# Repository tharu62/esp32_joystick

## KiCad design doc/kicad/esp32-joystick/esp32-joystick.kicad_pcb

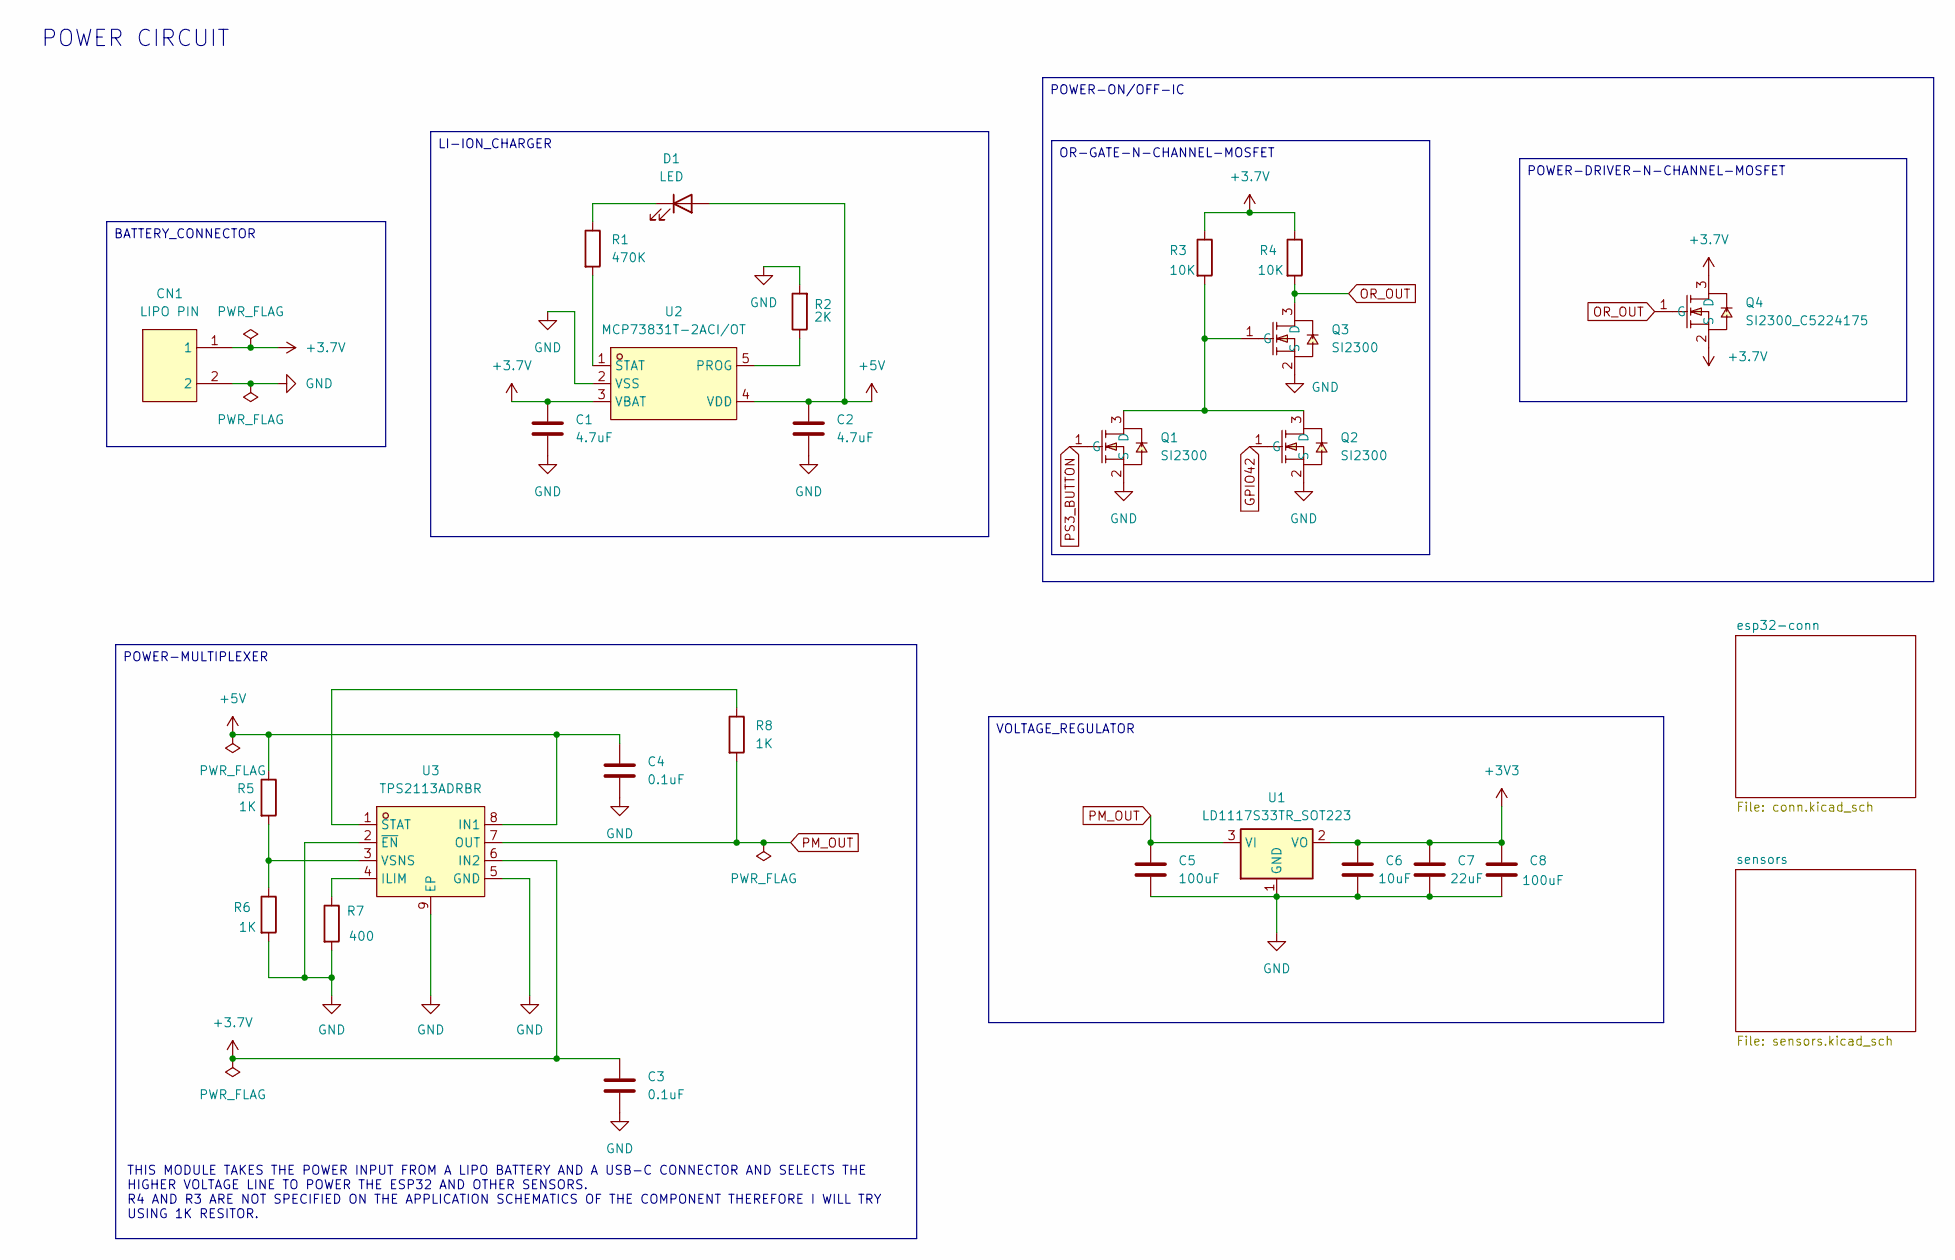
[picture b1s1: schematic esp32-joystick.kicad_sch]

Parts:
C1, C2: 4.7uF; C1206
C3, C4: 0.1uF; C1206
C5, C8: 100uF; C1206
C6: 10uF; C1206
C7: 22uF; C1206
CN1: LIPO PIN; CONN-TH_B2B-PH-K-S; LCSC Part C131337
D1: LED; LED1206-FD
Q1, Q2, Q3: SI2300; SOT-23-3_L2.9-W1.3-P1.90-LS2.4-BR; LCSC Part C5224175
Q4: SI2300_C5224175; SOT-23-3_L2.9-W1.3-P1.90-LS2.4-BR; LCSC Part C5224175
R1: 470K; R0603
R2: 2K; R0603
R3, R4: 10K; R0603
R5, R6, R8: 1K; R0603
R7: 400; R0805
U1: LD1117S33TR_SOT223; SOT-223-3_TabPin2
U2: MCP73831T-2ACI/OT; SOT-23-5_L3.0-W1.7-P0.95-LS2.8-BL; LCSC Part C424093
U3: TPS2113ADRBR; SON-8_L3.0-W3.0-P0.65-LS3.0-BL-EP; LCSC Part C354512

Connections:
+3.7V: C1.1, C3.1, CN1.1, Q4.2 (S), Q4.3 (D), R3.1, R4.1, U2.3 (VBAT), U3.6 (IN2)
+3V3: C6.1, C7.1, C8.1, U1.2 (VO); also elsewhere on the board
+5V: C2.1, C4.1, D1.2 (A), R5.1, U2.4 (VDD), U3.8 (IN1); also elsewhere on the board
GND: C1.2, C2.2, C3.2, C4.2, C5.2, C6.2, C7.2, C8.2, CN1.2, Q1.2 (S), Q2.2 (S), Q3.2 (S), R2.2, R6.2, R7.2, U1.1 (GND), U2.2 (VSS), U3.2 (~EN), U3.5 (GND), U3.9 (EP); also elsewhere on the board
GPIO42: Q2.1 (G); also elsewhere on the board
unnamed: D1.1 (K), R1.1
unnamed: Q1.3 (D), Q2.3 (D), Q3.1 (G), R3.2
unnamed: R2.1, U2.5 (PROG)
unnamed: R1.2, U2.1 (STAT)
unnamed: R7.1, U3.4 (ILIM)
unnamed: R8.1, U3.1 (STAT)
unnamed: R5.2, R6.1, U3.3 (VSNS)
OR_OUT: Q3.3 (D), Q4.1 (G), R4.2
PM_OUT: C5.1, R8.2, U1.3 (VI), U3.7 (OUT)
PS3_BUTTON: Q1.1 (G); also elsewhere on the board

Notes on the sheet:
THIS MODULE TAKES THE POWER INPUT FROM A LIPO BATTERY AND A USB-C CONNECTOR AND SELECTS THE HIGHER VOLTAGE LINE TO POWER THE ESP32 AND OTHER SENSORS. R4 AND R3 ARE NOT SPECIFIED ON THE APPLICATION SCHEMATICS OF THE COMPONENT THEREFORE I WILL TRY USING 1K RESITOR.
POWER CIRCUIT
POWER-MULTIPLEXER
OR-GATE-N-CHANNEL-MOSFET
VOLTAGE_REGULATOR
BATTERY_CONNECTOR
POWER-DRIVER-N-CHANNEL-MOSFET
POWER-ON/OFF-IC
LI-ION_CHARGER

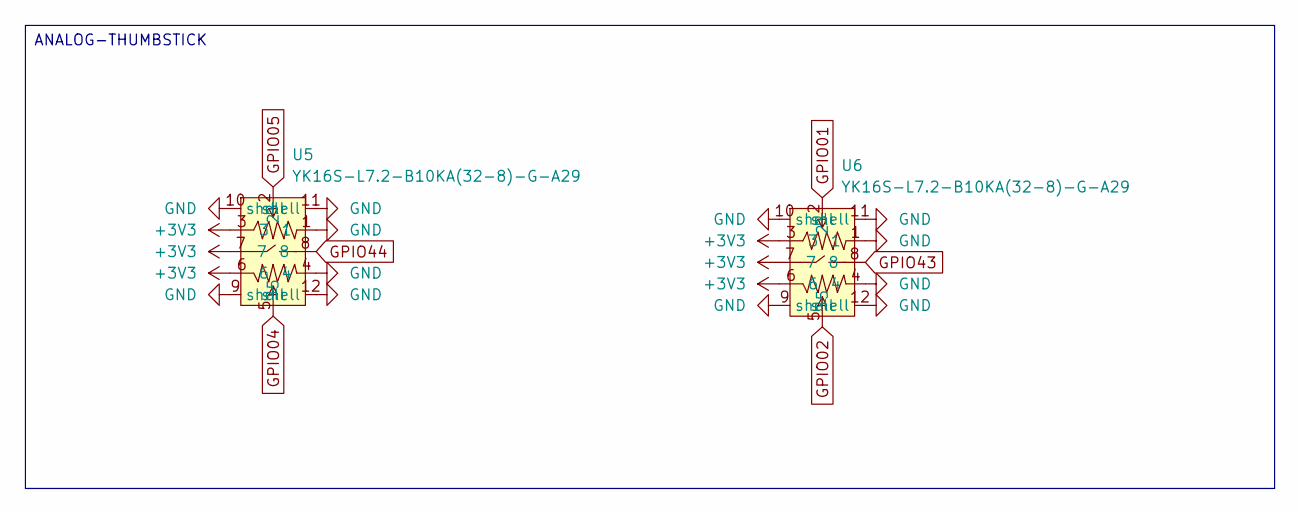
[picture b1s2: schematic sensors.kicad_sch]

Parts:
U5, U6: YK16S-L7.2-B10KA(32-8)-G-A29; JOYTICK-TH_YF16S-FL7.2-B5KB-45-10-Y_1; LCSC Part C37323746

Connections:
+3V3: U5.3, U5.6, U5.7, U6.3, U6.6, U6.7; also elsewhere on the board
GND: U5.1, U5.4, U5.9 (shell), U5.10 (shell), U5.11 (shell), U5.12 (shell), U6.1, U6.4, U6.9 (shell), U6.10 (shell), U6.11 (shell), U6.12 (shell); also elsewhere on the board
GPIO01: U6.2; also elsewhere on the board
GPIO02: U6.5; also elsewhere on the board
GPIO04: U5.5; also elsewhere on the board
GPIO05: U5.2; also elsewhere on the board
GPIO43: U6.8; also elsewhere on the board
GPIO44: U5.8; also elsewhere on the board

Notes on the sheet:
ANALOG-THUMBSTICK

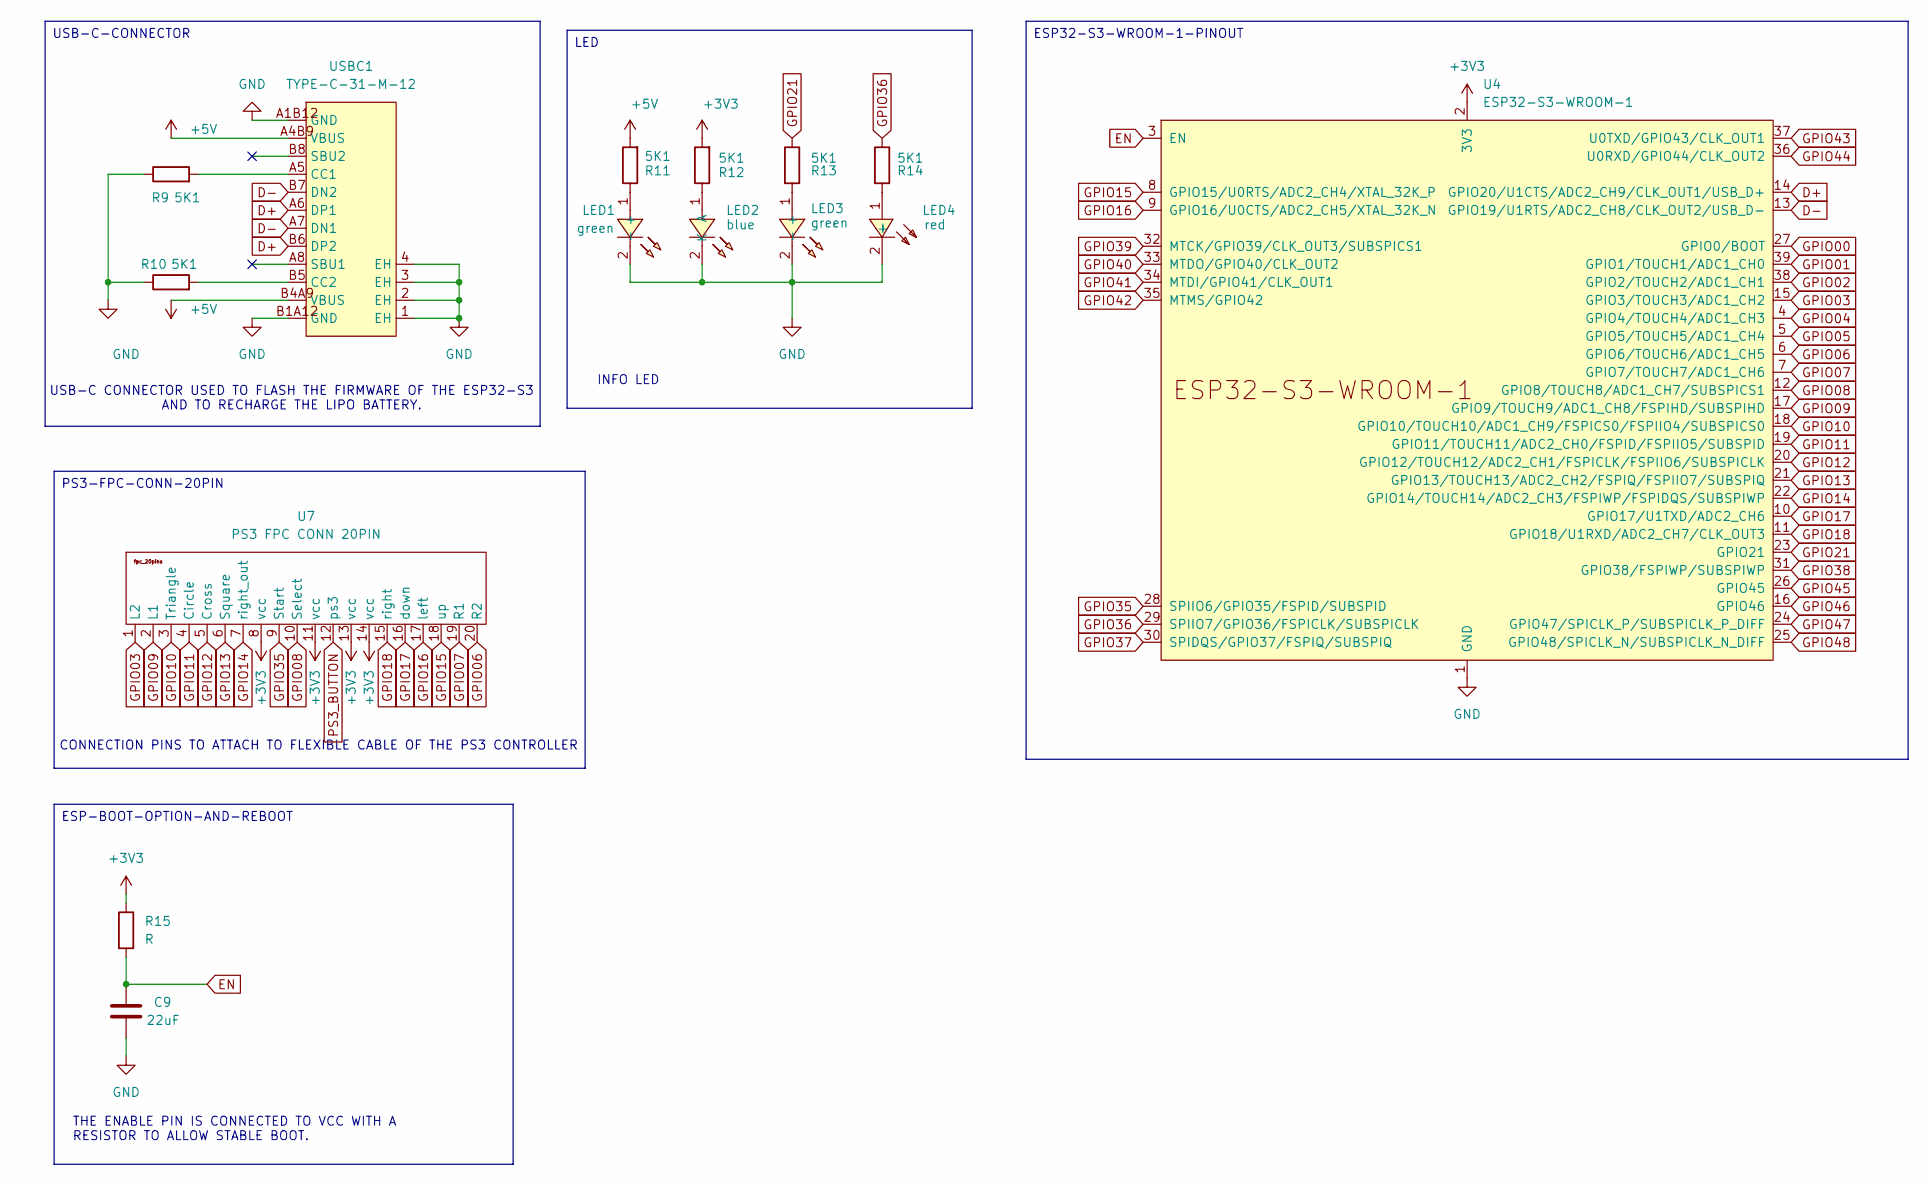
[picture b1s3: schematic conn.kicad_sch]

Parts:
C9: 22uF; C1206
LED1, LED3: green; LED0603-FD; LCSC Part C19273151
LED2: blue; LED0603-FD; LCSC Part C19171394
LED4: red; LED0603-FD; LCSC Part C19171390
R9, R10, R11, R12, R13, R14: 5K1; R0603
R15: R; R0603
U4: ESP32-S3-WROOM-1
U7: PS3 FPC CONN 20PIN; ps3_fpc_conn_20pin
USBC1: TYPE-C-31-M-12; USB-C_SMD-TYPE-C-31-M-12_1; LCSC Part C165948

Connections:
+3V3: R12.2, R15.1, U4.2 (3V3), U7.8 (vcc), U7.11 (vcc), U7.13 (vcc), U7.14 (vcc); also elsewhere on the board
+5V: R11.2, USBC1.A4B9 (VBUS), USBC1.B4A9 (VBUS); also elsewhere on the board
D+: U4.14 (GPIO20/U1CTS/ADC2_CH9/CLK_OUT1/USB_D+), USBC1.A6 (DP1), USBC1.B6 (DP2)
D-: U4.13 (GPIO19/U1RTS/ADC2_CH8/CLK_OUT2/USB_D-), USBC1.A7 (DN1), USBC1.B7 (DN2)
EN: C9.1, R15.2, U4.3 (EN)
GND: C9.2, LED1.2 (-), LED2.2 (K), LED3.2 (-), LED4.2 (-), R9.1, R10.1, U4.1 (GND), U4.40 (GND), U4.41 (GND), USBC1.1 (EH), USBC1.2 (EH), USBC1.3 (EH), USBC1.4 (EH), USBC1.A1B12 (GND), USBC1.B1A12 (GND); also elsewhere on the board
GPIO00: U4.27 (GPIO0/BOOT)
GPIO01: U4.39 (GPIO1/TOUCH1/ADC1_CH0); also elsewhere on the board
GPIO02: U4.38 (GPIO2/TOUCH2/ADC1_CH1); also elsewhere on the board
GPIO03: U4.15 (GPIO3/TOUCH3/ADC1_CH2), U7.1 (L2)
GPIO04: U4.4 (GPIO4/TOUCH4/ADC1_CH3); also elsewhere on the board
GPIO05: U4.5 (GPIO5/TOUCH5/ADC1_CH4); also elsewhere on the board
GPIO06: U4.6 (GPIO6/TOUCH6/ADC1_CH5), U7.20 (R2)
GPIO07: U4.7 (GPIO7/TOUCH7/ADC1_CH6), U7.19 (R1)
GPIO08: U4.12 (GPIO8/TOUCH8/ADC1_CH7/SUBSPICS1), U7.10 (Select)
GPIO09: U4.17 (GPIO9/TOUCH9/ADC1_CH8/FSPIHD/SUBSPIHD), U7.2 (L1)
GPIO10: U4.18 (GPIO10/TOUCH10/ADC1_CH9/FSPICS0/FSPIIO4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), U7.3 (Triangle)
GPIO11: U4.19 (GPIO11/TOUCH11/ADC2_CH0/FSPID/FSPIIO5/S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), U7.4 (Circle)
GPIO12: U4.20 (GPIO12/TOUCH12/ADC2_CH1/FSPICLK/FSPIIO6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), U7.5 (Cross)
GPIO13: U4.21 (GPIO13/TOUCH13/ADC2_CH2/FSPIQ/FSPIIO7/S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), U7.6 (Square)
GPIO14: U4.22 (GPIO14/TOUCH14/ADC2_CH3/FSPIWP/FSPIDQS/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), U7.7 (right_out)
GPIO15: U4.8 (GPIO15/U0RTS/ADC2_CH4/XTAL_32K_P), U7.18 (up)
GPIO16: U4.9 (GPIO16/U0CTS/ADC2_CH5/XTAL_32K_N), U7.17 (left)
GPIO17: U4.10 (GPIO17/U1TXD/ADC2_CH6), U7.16 (down)
GPIO18: U4.11 (GPIO18/U1RXD/ADC2_CH7/CLK_OUT3), U7.15 (right)
GPIO21: R13.1, U4.23 (GPIO21)
GPIO35: U4.28 (SPIIO6/GPIO35/FSPID/SUBSPID), U7.9 (Start)
GPIO36: R14.1, U4.29 (SPIIO7/GPIO36/FSPICLK/SUBSPICLK)
GPIO37: U4.30 (SPIDQS/GPIO37/FSPIQ/SUBSPIQ)
GPIO38: U4.31 (GPIO38/FSPIWP/SUBSPIWP)
GPIO39: U4.32 (MTCK/GPIO39/CLK_OUT3/SUBSPICS1)
GPIO40: U4.33 (MTDO/GPIO40/CLK_OUT2)
GPIO41: U4.34 (MTDI/GPIO41/CLK_OUT1)
GPIO42: U4.35 (MTMS/GPIO42); also elsewhere on the board
GPIO43: U4.37 (U0TXD/GPIO43/CLK_OUT1); also elsewhere on the board
GPIO44: U4.36 (U0RXD/GPIO44/CLK_OUT2); also elsewhere on the board
GPIO45: U4.26 (GPIO45)
GPIO46: U4.16 (GPIO46)
GPIO47: U4.24 (GPIO47/SPICLK_P/SUBSPICLK_P_DIFF)
GPIO48: U4.25 (GPIO48/SPICLK_N/SUBSPICLK_N_DIFF)
unnamed 42: LED1.1 (+), R11.1; also elsewhere on the board
unnamed 43: LED2.1 (A), R12.1; also elsewhere on the board
unnamed: LED3.1 (+), R13.2
unnamed: LED4.1 (+), R14.2
unnamed: R9.2, USBC1.A5 (CC1)
unnamed: R10.2, USBC1.B5 (CC2)
PS3_BUTTON: U7.12 (ps3); also elsewhere on the board

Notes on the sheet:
THE ENABLE PIN IS CONNECTED TO VCC WITH A RESISTOR TO ALLOW STABLE BOOT.
USB-C CONNECTOR USED TO FLASH THE FIRMWARE OF THE ESP32-S3 AND TO RECHARGE THE LIPO BATTERY.
CONNECTION PINS TO ATTACH TO FLEXIBLE CABLE OF THE PS3 CONTROLLER
INFO LED
PS3-FPC-CONN-20PIN
USB-C-CONNECTOR
LED
ESP32-S3-WROOM-1-PINOUT
ESP-BOOT-OPTION-AND-REBOOT

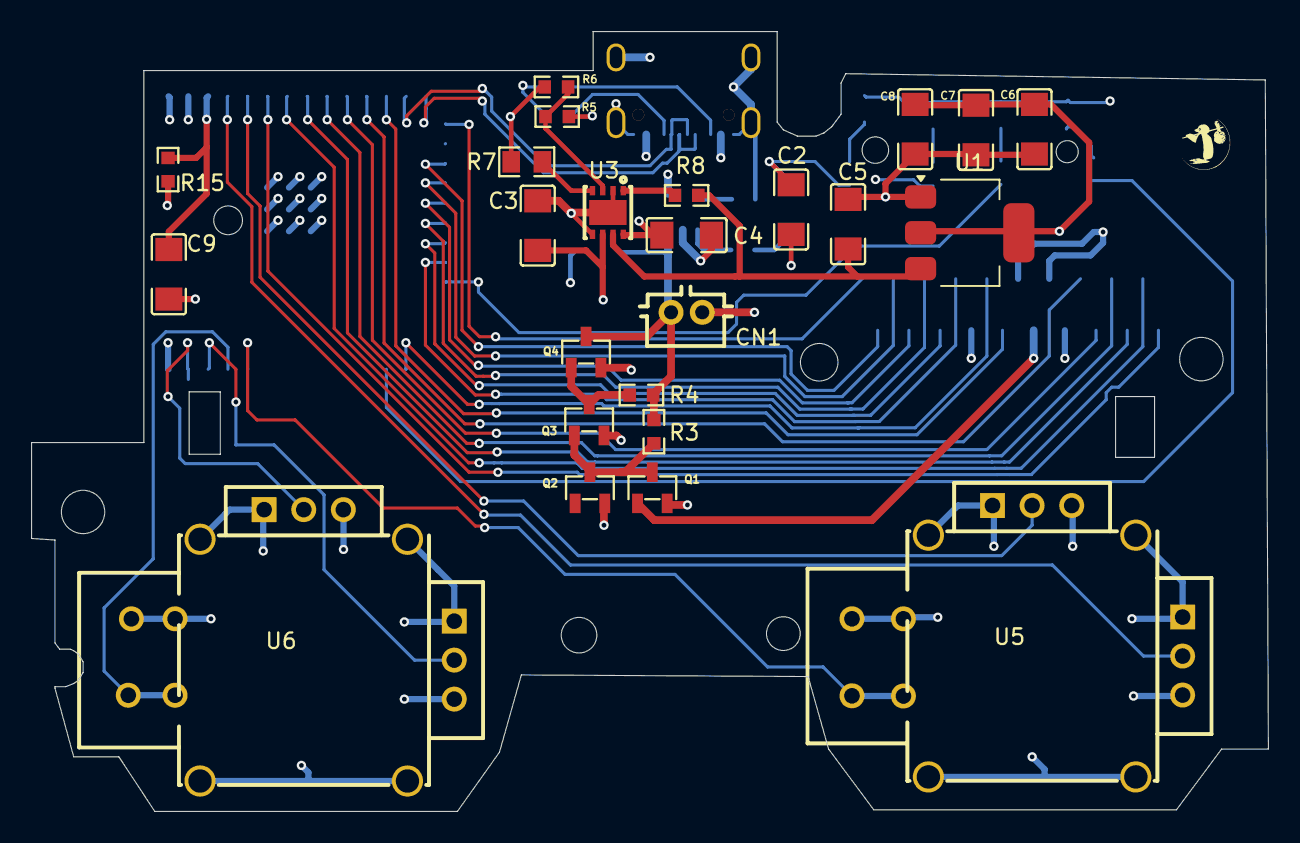
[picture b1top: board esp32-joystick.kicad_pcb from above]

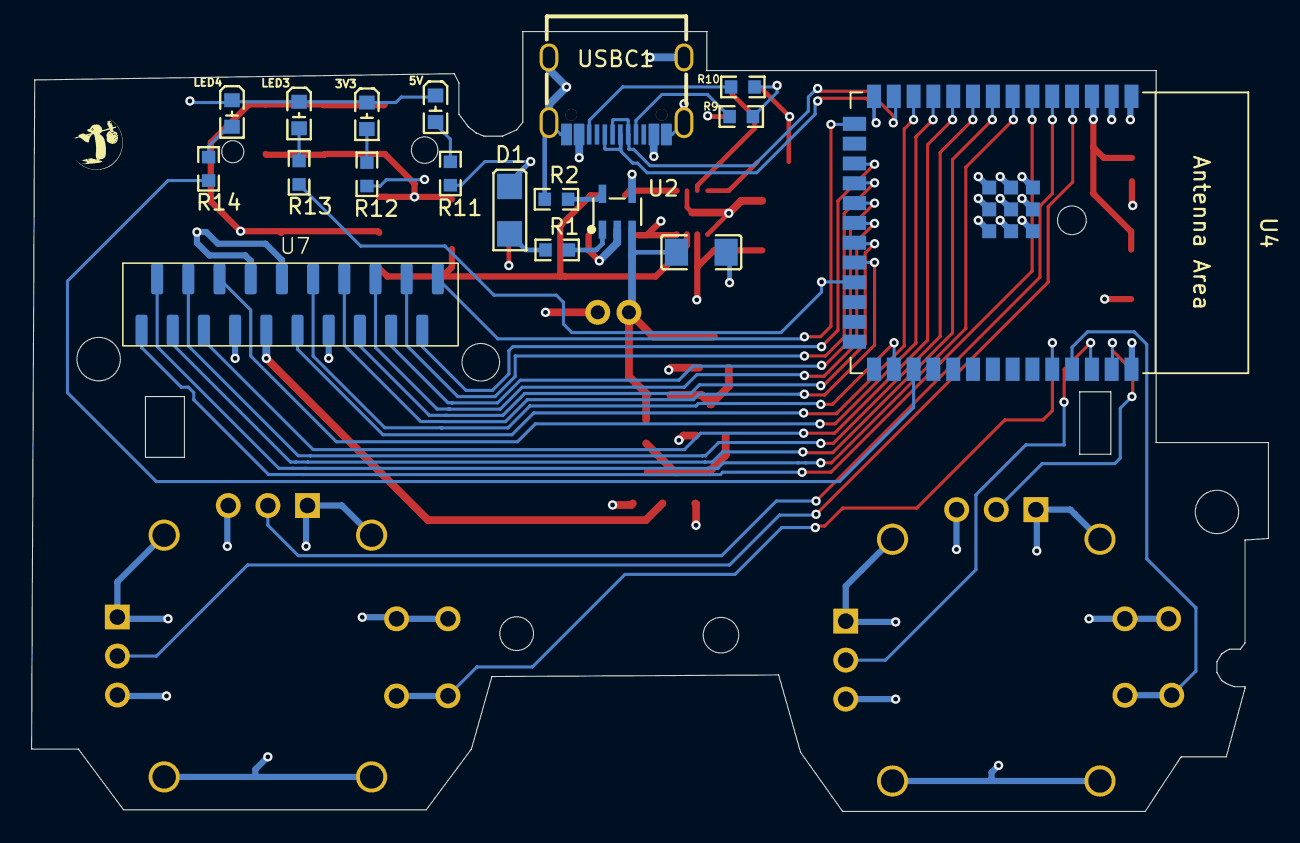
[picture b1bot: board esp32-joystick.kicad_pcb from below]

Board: 4 copper layers, 79.3 x 50.0 mm, 42 parts (18 on the bottom side), 47 nets.

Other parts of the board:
3V3: blue; LED0603-FD
5V: green; LED0603-FD

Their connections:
GND: 3V3.2 (K), 5V.2 (-); also elsewhere on the board
unnamed 42: 5V.1 (+); also elsewhere on the board
unnamed 43: 3V3.1 (A); also elsewhere on the board

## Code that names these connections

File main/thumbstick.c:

#include "thumbstick.h"

#define TAG "JOY_MASTER"

// ESP32-S3 ADC
#define ADC_UNIT              ADC_UNIT_1
#define THROTTLE_ADC_CHANNEL  ADC_CHANNEL_3   // GPIO04
#define ROLL_ADC_CHANNEL      ADC_CHANNEL_0   // GPIO1
#define PITCH_ADC_CHANNEL     ADC_CHANNEL_1   // GPIO02
#define YAW_ADC_CHANNEL       ADC_CHANNEL_4   // GPIO05
#define ADC_MAX               4095.0f

static adc_oneshot_unit_handle_t adc_handle;

void adc_init_throttle(void)
{
    adc_oneshot_unit_init_cfg_t unit_cfg = {
        .unit_id = ADC_UNIT,
    };
    ESP_ERROR_CHECK(adc_oneshot_new_unit(&unit_cfg, &adc_handle));

    adc_oneshot_chan_cfg_t chan_cfg = {
        .bitwidth = ADC_BITWIDTH_12,
        .atten = ADC_ATTEN_DB_12,   // <-- CORRECT FOR IDF 5.x
    };
    ESP_ERROR_CHECK(adc_oneshot_config_channel(
        adc_handle,
        THROTTLE_ADC_CHANNEL,
        &chan_cfg
    ));

    // ESP_LOGI(TAG, "ADC initialized (GPIO10)");
}

void init_adc_all(void)
{
    adc_oneshot_unit_init_cfg_t unit_cfg = {
        .unit_id = ADC_UNIT,
    };
    ESP_ERROR_CHECK(adc_oneshot_new_unit(&unit_cfg, &adc_handle));

    adc_oneshot_chan_cfg_t chan_cfg = {
        .bitwidth = ADC_BITWIDTH_12,
        .atten = ADC_ATTEN_DB_12,
    };
    
    // Configure throttle channel
    ESP_ERROR_CHECK(adc_oneshot_config_channel(
        adc_handle,
        THROTTLE_ADC_CHANNEL,
        &chan_cfg
    ));
    
    // Configure roll channel
    ESP_ERROR_CHECK(adc_oneshot_config_channel(
        adc_handle,
        ROLL_ADC_CHANNEL,
        &chan_cfg
    ));
    
    // Configure pitch channel
    ESP_ERROR_CHECK(adc_oneshot_config_channel(
        adc_handle,
        PITCH_ADC_CHANNEL,
        &chan_cfg
    ));

    // Configure yaw channel
    ESP_ERROR_CHECK(adc_oneshot_config_channel(
        adc_handle,
        YAW_ADC_CHANNEL,
        &chan_cfg
    ));
    
    ESP_LOGI(TAG, "ADC initialized for all channels");
}

float read_throttle(void)
{
    int raw = 0;
    adc_oneshot_read(adc_handle, THROTTLE_ADC_CHANNEL, &raw);
    if (raw < 0) raw = 0;
    if (raw > ADC_MAX) raw = ADC_MAX;
    // Throttle is wired inverted: forward is lower voltage.
    float t = 1.0f - raw / ADC_MAX;
    return t;
}

float read_roll(void)
{
    int raw = 0;
    adc_oneshot_read(adc_handle, ROLL_ADC_CHANNEL, &raw);
    if (raw < 0) raw = 0;
    if (raw > ADC_MAX) raw = ADC_MAX;
    float r = 1.0f - (raw / ADC_MAX);
    return r;
}

float read_pitch(void)
{
    int raw = 0;
    adc_oneshot_read(adc_handle, PITCH_ADC_CHANNEL, &raw);
    if (raw < 0) raw = 0;
    if (raw > ADC_MAX) raw = ADC_MAX;
    float p = (raw / ADC_MAX);
    return p;
}

float read_yaw(void)
{
    int raw = 0;
    adc_oneshot_read(adc_handle, YAW_ADC_CHANNEL, &raw);
    if (raw < 0) raw = 0;
    if (raw > ADC_MAX) raw = ADC_MAX;    
    float y = (raw / ADC_MAX);
    return y;
}

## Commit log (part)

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2026-05-09 resolved blocking in debug print and better clamping of data.
